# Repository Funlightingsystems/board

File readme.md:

# Board
Includes the configuration utility, among other things. A more organized version is available here: 

[New link](https://github.com/funeventsystems/Audio-Mixing-Board)

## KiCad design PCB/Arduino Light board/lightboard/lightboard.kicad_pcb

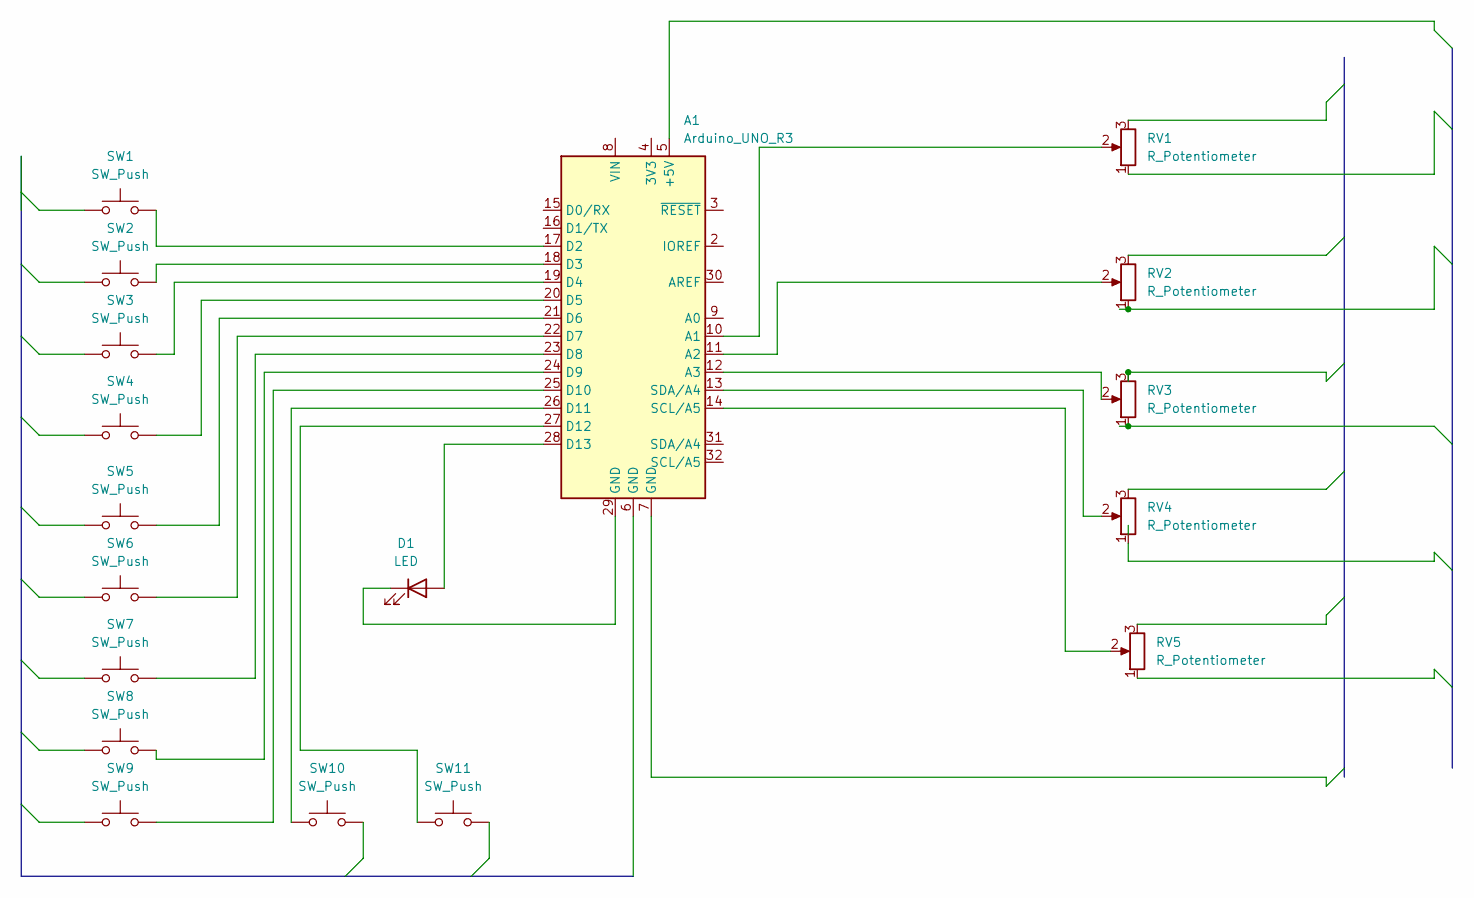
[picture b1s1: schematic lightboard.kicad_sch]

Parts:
A1: Arduino_UNO_R3
D1: LED; LED_D1.8mm_W1.8mm_H2.4mm_Horizontal_O1.27mm_Z4.9mm
RV1, RV2, RV3, RV4, RV5: R_Potentiometer; Potentiometer_ACP_CA14-VSMD_Vertical_Hole
SW1, SW2, SW3, SW4, SW5, SW6, SW7, SW8, SW9, SW10, SW11: SW_Push; SW_Push_SPST_NO_Alps_SKRK

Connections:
unnamed: A1.10 (A1), RV1.2
unnamed: A1.11 (A2), RV2.2
unnamed: A1.12 (A3), RV3.2
unnamed: A1.17 (D2), SW1.2
unnamed: A1.18 (D3), SW2.2
unnamed: A1.19 (D4), SW3.2
unnamed: A1.20 (D5), SW4.2
unnamed: A1.21 (D6), SW5.2
unnamed: A1.22 (D7), SW6.2
unnamed: A1.23 (D8), SW7.2
unnamed: A1.24 (D9), SW8.2
unnamed: A1.25 (D10), SW9.2
unnamed: A1.26 (D11), SW10.1
unnamed: A1.27 (D12), SW11.1
unnamed: A1.28 (D13), D1.2 (A)
unnamed: A1.14 (SCL/A5), RV5.2
unnamed: A1.13 (SDA/A4), RV4.2
unnamed: A1.29 (GND), D1.1 (K)

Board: 2 copper layers, 18 parts (0 on the bottom side), 18 nets, no tracks yet.

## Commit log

2023-06-05 Hello
    t
2023-06-05 Added Readme
    t
2023-06-05 Added some inspiration files
2023-06-13 Added a simple version of the websocket
    Added a simple version of the websocket
2023-06-17 Added some more stuff
2023-06-17 added even more stuff
2023-06-17 added yet some more files
2023-06-20 Added many things
2023-06-20 Added some pics of the stagecl
    I remember most things about this console so ask me questions!
2023-06-20 Added the whole configuration system. Soon to add a desktop app(?)
2023-06-20 Added some useless files by accident
2023-06-20 Trying to fix the readme file
2023-06-20 one last formatting error
2023-06-21 Adding styling
2023-06-21 updated some new stuff to work with IP addresses and domain names instead of running from the localhost,.
2023-06-21 Added the cors module
2023-06-22 Added the lights code
2023-06-22 Things
    Moved around some files to keep it organized. I then added the waffle navigation on the config page, and added a grid layout to show the data in an appealing way.
2023-06-22 Documentation Stuff
2023-06-22 Documentation
2023-06-22 aaaaaa
2023-06-22 [ImgBot] Optimize images
    *Total -- 44,306.40kb -> 38,541.26kb (13.01%)
    /Unity Files/DMXController/Library/PackageCache/com.unity.settings-manager@1.0.3/Content/Options.png -- 14.70kb -> 2.71kb (81.55%)
    /Unity Files/DMXController/Library/PackageCache/com.unity.ugui@1.0.0/Documentation~/images/UI_ScrollRectHierarchy.png -- 18.84kb -> 3.94kb (79.11%)
    /Unity Files/DMXController/Library/PackageCache/com.unity.ugui@1.0.0/Documentation~/images/UI_DropdownHierarchySimple.png -- 19.52kb -> 5.00kb (74.37%)
    /Unity Files/DMXController/Library/PackageCache/com.unity.ugui@1.0.0/Documentation~/images/UI_DropdownHierarchyScrolling.png -- 22.50kb -> 6.00kb (73.34%)
    /Unity Files/DMXController/Library/Package
2023-06-22 Ummmm, I guess I ran the documentation command. ;)
    Sorry about the weird formatting, I just committed to master. You know I am going to link everyone to this to make it look like I didn't fully make the mistake. 8664 file!
2023-06-22 aaaaaaaaaaaaaaaaaaaaaaaaa
2023-06-22 Undoing a bunch of stuff.
2023-06-22 Docs
2023-06-23 Added some more documentation stuff
2023-06-23 Added the KiCad files
2023-06-23 PDF stuff
2023-06-23 added weasyprint
2023-06-23 Fixed the documentation
2023-06-25 Manual and other stuff
2023-06-25 Bump mkdocs from 1.2.2 to 1.2.3 in /docs
    Bumps [mkdocs](https://github.com/mkdocs/mkdocs) from 1.2.2 to 1.2.3.
    - [Release notes](https://github.com/mkdocs/mkdocs/releases)
    - [Commits](https://github.com/mkdocs/mkdocs/compare/1.2.2...1.2.3)
    ---
    updated-dependencies:
    - dependency-name: mkdocs
2023-06-25 Bump mkdocs from 1.2.2 to 1.2.3 in /site
    Bumps [mkdocs](https://github.com/mkdocs/mkdocs) from 1.2.2 to 1.2.3.
    - [Release notes](https://github.com/mkdocs/mkdocs/releases)
    - [Commits](https://github.com/mkdocs/mkdocs/compare/1.2.2...1.2.3)
    ---
    updated-dependencies:
    - dependency-name: mkdocs
2023-07-28 Removed the unity application from the repo, to reduce filesize.
    This will make it easier to install for people. I will move the unity stuff to another repo, I will link the unity repo in the readme or some equivalent.
2023-08-07 Stuff
2024-01-11 Bump jinja2 from 3.0.1 to 3.1.3 in /docs
    Bumps [jinja2](https://github.com/pallets/jinja) from 3.0.1 to 3.1.3.
    - [Release notes](https://github.com/pallets/jinja/releases)
    - [Changelog](https://github.com/pallets/jinja/blob/main/CHANGES.rst)
    - [Commits](https://github.com/pallets/jinja/compare/3.0.1...3.1.3)
    ---
    updated-dependencies:
2024-01-11 Bump jinja2 from 3.0.1 to 3.1.3 in /site
    Bumps [jinja2](https://github.com/pallets/jinja) from 3.0.1 to 3.1.3.
    - [Release notes](https://github.com/pallets/jinja/releases)
    - [Changelog](https://github.com/pallets/jinja/blob/main/CHANGES.rst)
    - [Commits](https://github.com/pallets/jinja/compare/3.0.1...3.1.3)
    ---
    updated-dependencies:
2024-03-29 Bump express from 4.18.2 to 4.19.2 in /NodeJS
    Bumps [express](https://github.com/expressjs/express) from 4.18.2 to 4.19.2.
    - [Release notes](https://github.com/expressjs/express/releases)
    - [Changelog](https://github.com/expressjs/express/blob/master/History.md)
    - [Commits](https://github.com/expressjs/express/compare/4.18.2...4.19.2)
    ---
    updated-dependencies:
2024-03-29 Bump express in /Monitoring System/Console Based/monitor
    Bumps [express](https://github.com/expressjs/express) from 4.18.2 to 4.19.2.
    - [Release notes](https://github.com/expressjs/express/releases)
    - [Changelog](https://github.com/expressjs/express/blob/master/History.md)
    - [Commits](https://github.com/expressjs/express/compare/4.18.2...4.19.2)
    ---
    updated-dependencies:
2024-03-29 Bump express from 4.18.2 to 4.19.2 in /Configuration Software
    Bumps [express](https://github.com/expressjs/express) from 4.18.2 to 4.19.2.
    - [Release notes](https://github.com/expressjs/express/releases)
    - [Changelog](https://github.com/expressjs/express/blob/master/History.md)
    - [Commits](https://github.com/expressjs/express/compare/4.18.2...4.19.2)
    ---
    updated-dependencies:
